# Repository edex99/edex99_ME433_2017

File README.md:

Eric Dexheimer
3/27/2017

First Repository

Another line

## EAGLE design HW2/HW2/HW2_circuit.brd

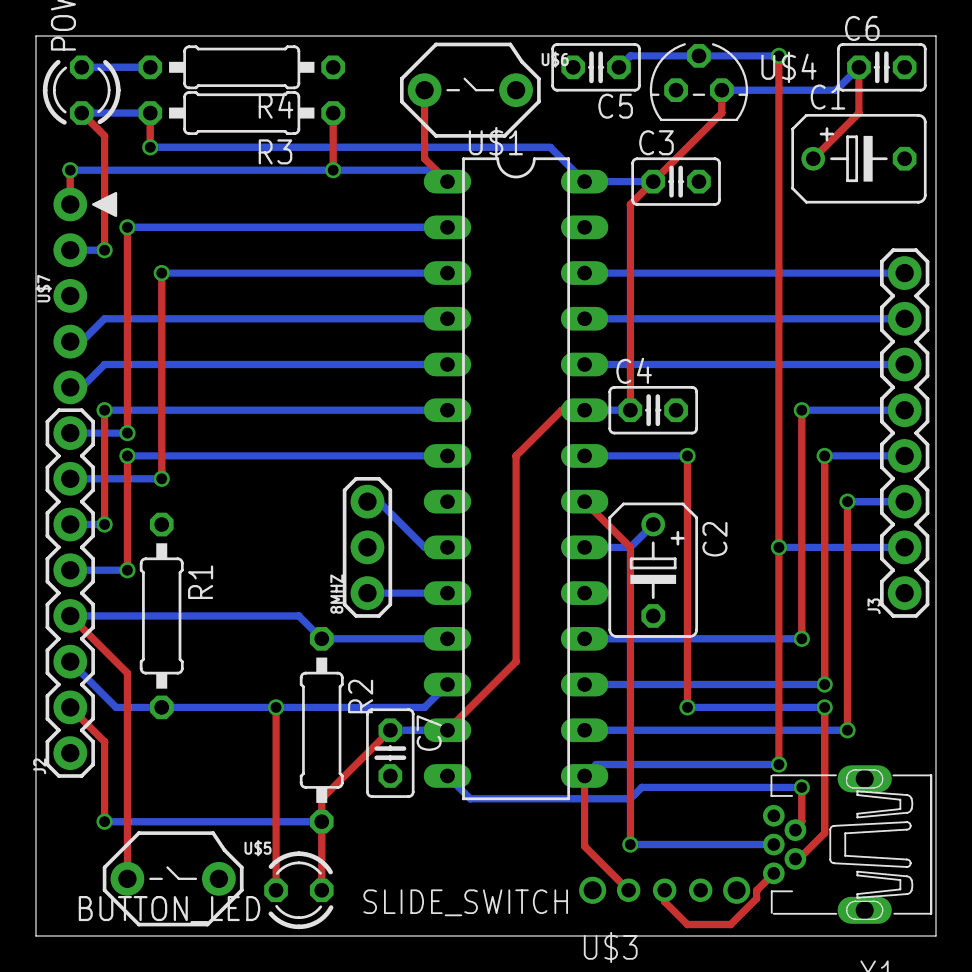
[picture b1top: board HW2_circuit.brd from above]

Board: 2 copper layers, 50.0 x 50.0 mm, 23 parts (0 on the bottom side), 26 nets.

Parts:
8MHZ: RESONATOR; OSCILLATOR
BUTTON_LED: GREEN; LED3MM
C1, C2: 10 uF; B45181B
C3, C4, C5, C6, C7: 0.1 uF; C025-025X050
J2: LEFT; 1X08
J3: RIGHT; 1X08
POWER_LED: RED; LED3MM
R1, R4: 330; 0207/10
R2, R3: 10k; 0207/10
U$1: PIC32MX250F128B; DIL28-3
U$3: SLIDE_SWITCH
U$4: MCP1702; TO92
U$5, U$6: BUTTON
U$7: PICKIT32
X1: MINI-USB_SHIELD5P2-32005-601; 32005-601

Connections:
+3V3: BUTTON_LED.A, C1.+, C3.1, C4.1, C6.1, C7.1, J2.2, POWER_LED.A, R2.2, R3.2, U$1.13, U$1.23, U$1.28, U$4.3, U$7.2
+5V: C5.1, J3.2, U$1.15, U$3.2, U$4.2
A0: J2.8, U$1.2
A1: J2.7, U$1.3
A4/LED: BUTTON_LED.K, J2.3, R1.2, U$1.12
B2: J2.6, U$1.6
B3: J2.5, U$1.7
B4/USER: J2.4, R2.1, U$1.11, U$5.1
B7: J3.3, U$1.16
B8: J3.4, U$1.17
B9: J3.5, U$1.18
B13: J3.6, U$1.24
B14: J3.7, U$1.25
B15: J3.8, U$1.26
D+: U$1.21, X1.3
D-: U$1.22, X1.2
GND: 8MHZ.2, C1.-, C2.-, C3.2, C4.2, C5.2, C6.2, C7.2, J2.1, J3.1, R1.1, R4.1, U$1.8, U$1.19, U$1.27, U$4.1, U$5.3, U$6.3, U$7.3, X1.5
MCLR: R3.1, U$1.1, U$6.1, U$7.1
unnamed: C2.+, U$1.20
unnamed: POWER_LED.K, R4.2
OSC1: 8MHZ.3, U$1.9
OSC2: 8MHZ.1, U$1.10
PGEC1: U$1.5, U$7.5
PGED1: U$1.4, U$7.4
USBID: U$1.14, X1.4
VBUS: U$3.3, X1.1

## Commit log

2017-03-28 My first commit!
2017-03-28 New line
    Added new line and ended file with new line character
2017-03-29 Main Template
    Copied provided template for start of main file
2017-03-29 Not in MPLAB X
    Created in text editor originally, but need to make this in MPLAB IDE
2017-03-29 Created HW1 folder
    Created HW1 folder through MPLAB X IDE and copied over the template
    into main.c
2017-03-29 DEVCFG0 Filled
    Input values for DEVCFG0
2017-03-29 DEVCFG1 Updated
2017-03-29 DEVCFG 2 and 3 Updated
2017-03-29 DEVCFG Register Keywords
    Switched all binary numbers to the keywords defined for the DEVCFG
    registers
2017-03-29 Button and LED Implementation
    Set TRIS and LAT for LED and button. Added while loop for toggle of
    LED and for halting when button is pressed.
2017-03-29 Resolved Timing Issue
    Changed loop such that after button is released, LED toggle resumes
    from where it was in square wave, rather than reset to the beginning of
    the wave.
2017-03-29 NSCOPE Images
    Added NSCOPE images
2017-03-29 Breadboard Image
2017-03-29 Demo Video
2017-03-30 Circuit Diagram
2017-04-02 PIC32 and Voltage Regulator Symbols
2017-04-03 Most of Schematic
2017-04-03 Updated Library
    Changed PICKIT to only have 5 through holes, modified switch connector
    device to match data sheet, and changed switch and button symbols for
    better illustration.
2017-04-03 Updated Schematic Symbols
2017-04-03 Started Board Layout
2017-04-03 First Version of Layout
    Finished layout with no DRC errors
2017-04-03 Board Layout Complete
    Board layout is finished, passes DRC. Labels have been added.
2017-04-06 Gerber Files and Board
    Board silkscreen adjusted and bmp added. Gerber finals generated.
2017-04-06 HW3 Duplicate
    HW3 folder has same contents as HW2, created for formal reference.
2017-04-10 SPI Library
    Made SPI library and functions
2017-04-10 Sin and sawtooth waves
2017-04-10 Most of loop structure
2017-04-10 Fixed sawtooth timing
    Sawtooth now has twice the period of the sine wave
2017-04-10 Images Added
2017-04-11 Added demo video
2017-04-13 I2C library
2017-04-13 Main Loop
    Corrected main loop and any last references to I2C2 from I2C1
2017-04-13 Demo Video and Schematic
2017-04-14 Initialization and Write Character to LCD
2017-04-15 Write String, Counter, and Draw Bar
2017-04-17 Added FPS counter
    FPS is printed on LCD screen at frequency 5 Hz
2017-04-17 LCD Demo Video
2017-04-19 Read in IMU data
    Initialize IMU and print data to LCD screen
2017-04-19 Draw IMU bars
    x and y acceleration of IMU draw onto LCD and scaled by magnitude of
    acceleration
2017-04-19 Bar refresh correction
    Whole line with bar is no longer cleared, only up until the end of the
    screen from where the bar begins.
2017-04-21 HW8 Code and Demo
    HW8 is HW7 code in MPLAB harmony project
2017-04-28 HW9 Finished
    Modified USB state machine to only print 100 samples of IMU data when
    ‘r’ pressed. Timing was modified to print at 100 Hz.
2017-05-05 Print Filtered z accelerations to screen
    Filter math still needs to be updated
2017-05-05 Android HelloWorld
    Text and SeekBar displayed on screen
2017-05-07 Tuned filters and corrected calculation errors
    Tuned parameters of FIR and IIR to give better results. Corrected
    methods of calculations that yielded incorrect values of the filter.
2017-05-07 Controlled Mouse speed
    Mouse goes to bottom left at screen at medium to slow speed
2017-05-07 IMU Mouse Control
    Added IMU mouse control and tuned speed so that it is easily
    controllable
2017-05-12 HW14 PIC Code, HW13 and HW14 Android Code
    HW13 code uses 2 slider bars to threshold green pixels from red and
    blue pixel values. HW14 PIC code sets up CDC USB code to communicate
    with Android app. Android app creates view of data sent form PIC and a
    slider bar to set the number that can be sent to and returned from the
    PIC.
2017-05-30 Android Center of Mass and PIC Motor Control via Output Compare
    HW19 implements center of mass display for filtered pixels. HW18 uses
    output compare on PIC to control two motors given two pwm inputs from
    USB.
2017-05-31 Center of Mass via USB and Modified PWM calculations on PIC
    Android now sends a center of mass to the PIC. The PIC now calculates
    two PWM values based on one center of mass.
2017-06-03 Updated Center of Mass Calculation
    Calculates center of mass of entire road on image instead of one for
    each horizontal line
2017-06-06 Send raw PWM values from Android
    Android uses center of mass from whole image to calculate PWM values,
    which are sent directly to PIC.
2017-06-07 Added turn back if center of mass lost
    Robot continues turning the same speed if center of mass is lost.
2017-06-09 Vive comminication and gains tuning
    Added in vive capability, tuned gains for mechatronics lab, and allowed
    for communication from pic to Android for plotting vive data on map.
2017-06-09 More gains tuning
2017-06-09 Box and Wheel Images and STL Files
